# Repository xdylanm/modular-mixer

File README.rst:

Mixer+ Module
=============

The Mixer+ module includes a basic three channel mixer as well as an attenuverter with the option to add distortion to the output signal.

3 Channel Mixer
---------------

The 3 channel mixer is designed for a maximum of unit gain per channel. 

* DC coupled inputs
* Inverting and non-inverting outputs
* Simple output level indicator (red LED illuminates when :math:`V_{pp} \gtrapprox 9V`)

Attenuverter with Distortion
----------------------------

The input of the attenuverter is connected internally (normaled) to the non-inverting output of the mixer. The internal connection is broken when an external connection is made. The attenuverter output can be optionally distorted or offset with a DC voltage. 

* Input normaled to the non-inverting output of the mixer and is DC coupled
* Gain from -1 to 1
* Optional back-to-back diode distortion (dirty/clean switch)
* DC offset control adds -6 to +6V DC to output signal

References
----------

#. Moritz Klein, "Designing a 3-channel mixer with diode distortion from scratch", `Youtube <https://www.youtube.com/watch?v=q8tmUgaXrEQ>`_
#. Ray Wilson, "Ultra-Simple Mono Audio Mixer #1", `Music From Outer Space <https://musicfromouterspace.com/analogsynth_new/OLDIESBUTGOODIES/AUDIOMIXER/monomixer.html>`_

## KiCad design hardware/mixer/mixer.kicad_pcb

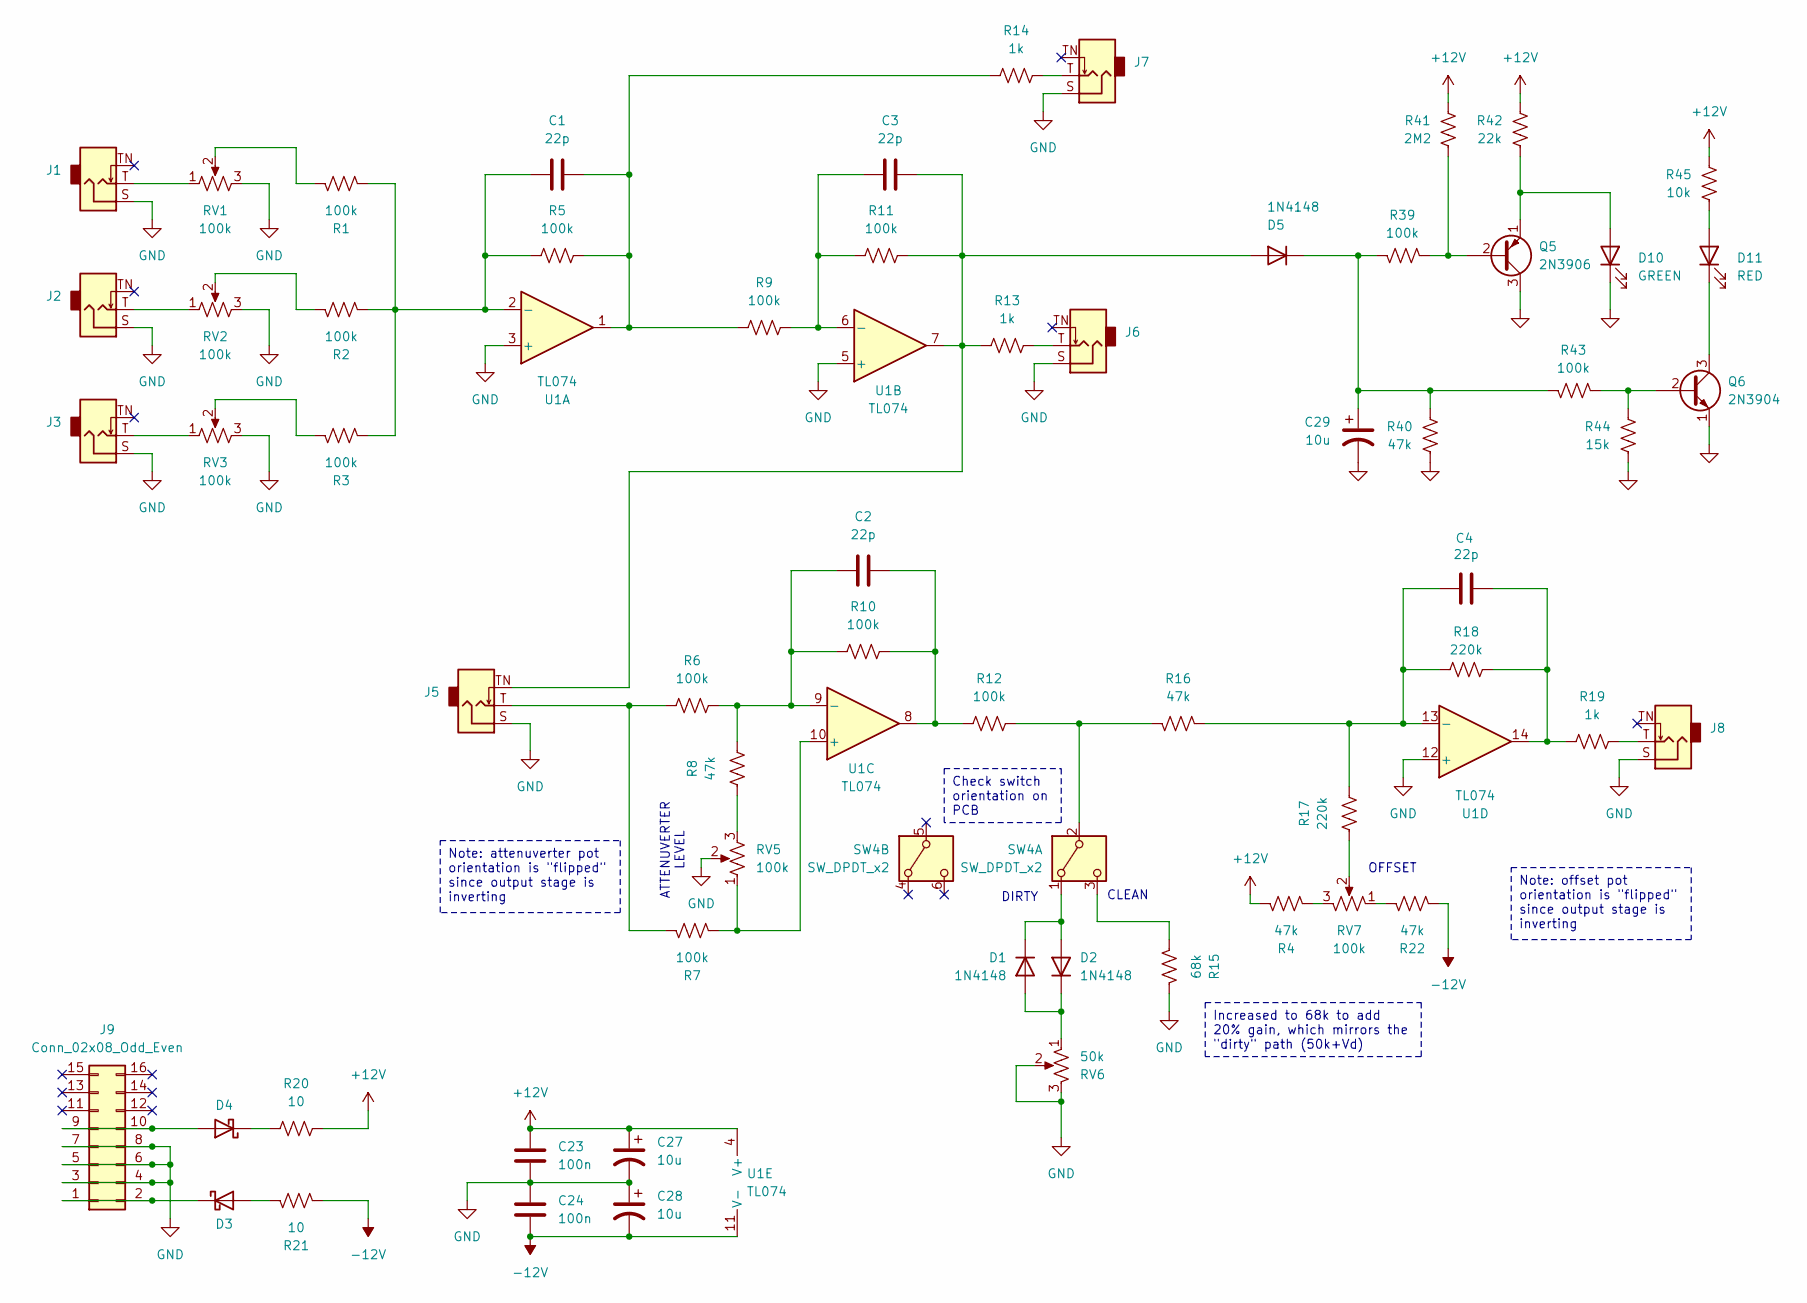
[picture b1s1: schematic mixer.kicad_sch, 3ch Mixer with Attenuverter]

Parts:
C1: 22p; C_Disc_D5.0mm_W2.5mm_P5.00mm
C2, C3, C4: 22p; C_Disc_D5.0mm_W2.5mm_P2.50mm
C23, C24: 100n; C_Disc_D5.0mm_W2.5mm_P2.50mm
C27, C28, C29: 10u; CP_Radial_D4.0mm_P2.00mm
D1, D2: 1N4148; D_DO-35_SOD27_P2.54mm_Vertical_AnodeUp
D3: D_Schottky; D_DO-41_SOD81_P2.54mm_Vertical_AnodeUp
D4: D_Schottky; D_DO-41_SOD81_P2.54mm_Vertical_KathodeUp
D5: 1N4148; D_DO-35_SOD27_P12.70mm_Horizontal
D10: GREEN; LED_D3.0mm_Clear
D11: RED; LED_D3.0mm_Clear
J1, J2, J3, J5, J6, J7, J8: AudioJack2_SwitchT; Jack_3.5mm_QingPu_WQP-PJ301M-12_Vertical
J9: Conn_02x08_Odd_Even; IDC-Header_2x08_P2.54mm_Vertical
Q5: 2N3906; TO-92_Inline_Wide
Q6: 2N3904; TO-92_Inline_Wide
R1, R2, R3, R5, R6, R7, R10, R11, R12, R39, R43: 100k; R_Axial_DIN0204_L3.6mm_D1.6mm_P2.54mm_Vertical
R4, R8, R22, R40: 47k; R_Axial_DIN0204_L3.6mm_D1.6mm_P2.54mm_Vertical
R9: 100k; R_Axial_DIN0207_L6.3mm_D2.5mm_P15.24mm_Horizontal
R13, R14, R19: 1k; R_Axial_DIN0204_L3.6mm_D1.6mm_P2.54mm_Vertical
R15: 68k; R_Axial_DIN0204_L3.6mm_D1.6mm_P2.54mm_Vertical
R16: 47k; R_Axial_DIN0207_L6.3mm_D2.5mm_P15.24mm_Horizontal
R17, R18: 220k; R_Axial_DIN0204_L3.6mm_D1.6mm_P2.54mm_Vertical
R20: 10; R_Axial_DIN0204_L3.6mm_D1.6mm_P2.54mm_Vertical
R21: 10; R_Axial_DIN0207_L6.3mm_D2.5mm_P10.16mm_Horizontal
R41: 2M2; R_Axial_DIN0204_L3.6mm_D1.6mm_P2.54mm_Vertical
R42: 22k; R_Axial_DIN0204_L3.6mm_D1.6mm_P2.54mm_Vertical
R44: 15k; R_Axial_DIN0204_L3.6mm_D1.6mm_P2.54mm_Vertical
R45: 10k; R_Axial_DIN0204_L3.6mm_D1.6mm_P2.54mm_Vertical
RV1, RV2, RV3, RV5, RV7: 100k; Potentiometer_Bourns_PTV09A-1_Single_Vertical
RV6: 50k; Potentiometer_Bourns_PTV09A-1_Single_Vertical
SW4: SW_DPDT_x2; SW_DPDT_13mm_x_13mm_P5.00mm
U1: TL074; DIP-14_W7.62mm_Socket

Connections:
+12V: C23.2, C27.1, R4.1, R20.2, R41.2, R42.2, R45.2, U1.4 (V+)
-12V: C24.1, C28.2, R21.2, R22.2, U1.11 (V-)
GND: C23.1, C24.2, C27.2, C28.1, C29.2, D10.1 (K), J1.S, J2.S, J3.S, J5.S, J6.S, J7.S, J8.S, J9.3, J9.4, J9.5, J9.6, J9.7, J9.8, Q5.3 (C), Q6.1 (E), R15.1, R40.1, R44.1, RV1.3, RV2.3, RV3.3, RV5.2, RV6.2, RV6.3, U1.3 (+), U1.5 (+), U1.12 (+)
unnamed: C1.2, R5.2, R9.1, R14.1, U1.1
unnamed: C2.2, R10.2, R12.1, U1.8
unnamed: C4.2, R18.2, R19.1, U1.14
unnamed: D1.2 (A), D2.1 (K), RV6.1
unnamed: D1.1 (K), D2.2 (A), SW4.1 (A)
unnamed: D3.2 (A), R21.1
unnamed: D3.1 (K), J9.1, J9.2
unnamed: D4.2 (A), J9.9, J9.10
unnamed: D4.1 (K), R20.1
unnamed: C3.2, D5.2 (A), J5.TN, R11.2, R13.1, U1.7
unnamed: C29.1, D5.1 (K), R39.2, R40.2, R43.2
unnamed: D10.2 (A), Q5.1 (E), R42.1
unnamed: D11.2 (A), R45.1
unnamed: D11.1 (K), Q6.3 (C)
unnamed: J1.T, RV1.1
unnamed: J2.T, RV2.1
unnamed: J3.T, RV3.1
unnamed: J5.T, R6.1, R7.1
unnamed: J6.T, R13.2
unnamed: J7.T, R14.2
unnamed: J8.T, R19.2
unnamed: Q5.2 (B), R39.1, R41.1
unnamed: Q6.2 (B), R43.1, R44.2
unnamed: R1.1, RV1.2
unnamed: R2.1, RV2.2
unnamed: R3.1, RV3.2
unnamed: R4.2, RV7.3
unnamed: R8.1, RV5.3
unnamed: R17.1, RV7.2
unnamed: R22.1, RV7.1
unnamed: R12.2, R16.2, SW4.2 (B)
unnamed: R15.2, SW4.3 (C)
unnamed: C1.1, R1.2, R2.2, R3.2, R5.1, U1.2 (-)
unnamed: C3.1, R9.2, R11.1, U1.6 (-)
unnamed: R7.2, RV5.1, U1.10 (+)
unnamed: C2.1, R6.2, R8.2, R10.1, U1.9 (-)
unnamed: C4.1, R16.1, R17.2, R18.1, U1.13 (-)

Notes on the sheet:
Increased to 68k to add 20% gain, which mirrors the "dirty" path (50k+Vd)
Note: attenuverter pot orientation is "flipped" since output stage is inverting
Note: offset pot orientation is "flipped" since output stage is inverting
Check switch orientation on PCB
CLEAN
ATTENUVERTER LEVEL
DIRTY
OFFSET

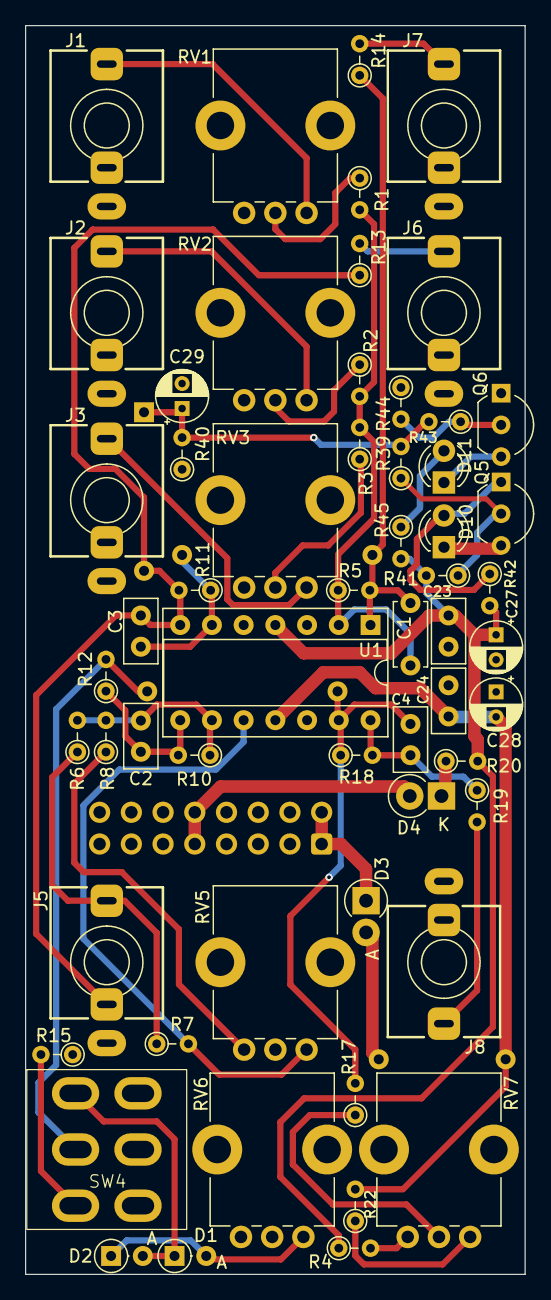
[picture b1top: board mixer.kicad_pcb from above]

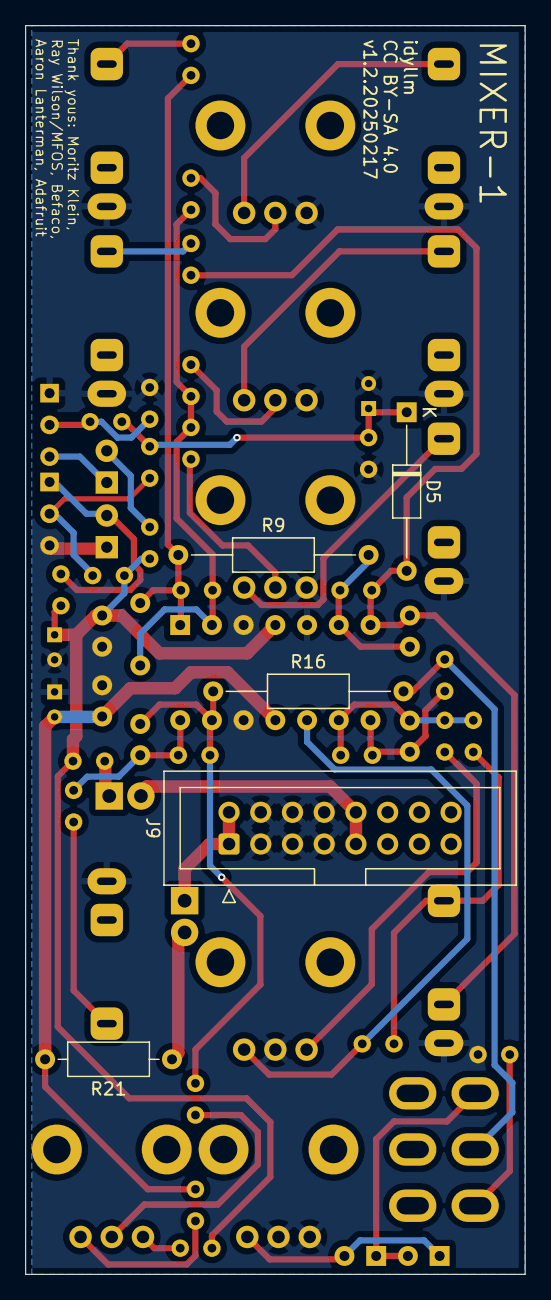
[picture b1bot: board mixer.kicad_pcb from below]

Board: 2 copper layers, 40.0 x 100.0 mm, 63 parts (5 on the bottom side), 40 nets.

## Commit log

2025-02-17 Moved mixer module from toolbox to own repo, updated docs based on 1.1 build
2025-02-17 added image of module
2025-02-18 changed R15 to 68k

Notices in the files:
hardware/mixer/mixer.kicad_pcb:
CC BY-SA 4.0
